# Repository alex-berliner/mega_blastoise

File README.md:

# mega_blastoise

**[▶ Play live](https://alex-berliner.github.io/mega_blastoise/battler/device.html)** — browser-based random battle simulator.
Everything published from this repo (the game, its UI notes, the hardware's 3D views) is linked from
[the site's front page](https://alex-berliner.github.io/mega_blastoise/), built from `site/`.

Layout:
- `crates/`: the Rust workspace. `ps_sim`, `ps_client`, `ps_dex`, `ps_protocol` (the Showdown
  port: server, client, dex and protocol), `ps_harness` (the protocol diff), `mega_blastoise_core` (no_std + battle data), `mega_blastoise_fw` (firmware), `mega_blastoise_test` (PC),
  and `mega_blastoise_web` (its own wasm workspace, the browser build).
- `hardware/`: the boards and cases ([index](hardware/README.md)). `docs/`: notes, including `docs/reference/architecture/`. `scripts/`: dev scripts.

Architecture overview: see [docs/reference/architecture/README.md](docs/reference/architecture/README.md).

## Documentation

Docs are in three folders: `docs/static/` (what the product is; changes only when that changes), `docs/reference/` (how it is built now) and `docs/living/` (plans, proposals and status).

- [docs/static/DESIGN.md](docs/static/DESIGN.md): what the product is, as Alex specified it. Start here
- [docs/static/next_spin_requirements.md](docs/static/next_spin_requirements.md): the next hardware spin's requirements and chosen parts
- [docs/reference/TECHNICAL.md](docs/reference/TECHNICAL.md): software internals, crate layout, interfaces, data flow
- [docs/reference/architecture/](docs/reference/architecture/README.md): deep-dive architecture docs
- [hardware/ref_design/](hardware/ref_design/README.md): the reference design (board, case, docs)
- [docs/reference/openscad-methodology.md](docs/reference/openscad-methodology.md): how the OpenSCAD cases are built and checked
- [docs/archive/v1/](docs/archive/v1/): the v1 device (Pico, two OLEDs, button matrix): its design and electronics notes.
  Its board, stripboard and case files were removed from the tree; tag `v1-archive` has them.

## Run modes (`mega-blastoise-test`)

The host binary is **interactive only**: stdin battle with the same **typed `BoardEvent` → `BoardEffects`** path as firmware (queue, prompts, combat log).

| Mode | Command | What it does |
|------|-----------|----------------|
| **Interactive** (default) | `cargo run -p mega-blastoise-test`<br>`cargo run -p mega-blastoise-test --release` | A Gen 1 battle on the PS engine over stdin (`1`-`4` a move, `s1`-`s6` a switch, when prompted). |
| **Automated tests** | `cargo test -p mega-blastoise-test` | Runs Rust tests (board-event parsing, scripted effect pipeline, host input stubs and full automated PS battles). Pass/fail exit status. |

Firmware (`mega-blastoise-fw`) has no CLI modes; flash and run as usual (see below).

## Compile

From this directory (`mega_blastoise/mega_blastoise/`, where the workspace `Cargo.toml` lives):

**PC test (host):**

```bash
cargo build -p mega-blastoise-test
cargo run -p mega-blastoise-test
```

Add `--release` to `cargo run` for a faster binary. See **Run modes** for `cargo test`.

**Firmware (Pico 2 / RP2350, the stripboard v2 board):** the Rust target is listed in
`rust-toolchain.toml`; install it by hand if rustup did not:

```bash
rustup target add thumbv8m.main-none-eabihf
```

Build from inside the firmware crate, so its `.cargo/config.toml` applies (default target
`thumbv8m.main-none-eabihf`, the linker scripts, the probe-rs runner). The default features
(`rp2350`, `board_v2`) are the device build:

```bash
cd crates/mega_blastoise_fw
cargo build
cargo build --release
cargo bv2          # same, plus the held-button overlay on the panel (input-debug)
```

**Firmware size stats** (prints section totals after link; install `rustup component add llvm-tools-preview` for `llvm-size`, or use `arm-none-eabi-size` from the GNU Arm toolchain):

```bash
./scripts/fw-build.sh                    # debug + llvm-size -t / -A
PROFILE=release ./scripts/fw-build.sh    # release build + stats
./scripts/fw-build.sh --release          # same (cargo passes --release)
```

Debug binaries include large `.debug_*` sections, so `llvm-size` totals look huge; prefer **`./scripts/fw-build.sh --release`** when checking flash/RAM against the Pico 2.

Flash/run with `probe-rs` as configured in `crates/mega_blastoise_fw/.cargo/config.toml`.

**Install `probe-rs`:** download and run the latest installer from the [probe-rs releases page](https://github.com/probe-rs/probe-rs/releases), then reload your shell:

```bash
curl --proto '=https' --tlsv1.2 -LsSf https://github.com/probe-rs/probe-rs/releases/latest/download/probe-rs-tools-installer.sh | sh
source ~/.bashrc   # or ~/.zshrc
```

Then flash with a debug probe connected (e.g. Picoprobe, CMSIS-DAP):

```bash
cd crates/mega_blastoise_fw
cargo run --release
```

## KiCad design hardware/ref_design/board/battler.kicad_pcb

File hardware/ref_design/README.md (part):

# Two-player handheld: reference design (REF-A)

A complete, orderable design for the production version of the handheld:
schematic, 2-layer board, JLCPCB fab and assembly files, a printable case, and
the documents to build, bring up and review it.

This board was first routed with `route.py 80`; 20 passes do as
well (2026-10-21: Freerouting leaves the same connections open after 15 as after 80).

**This is the 2-layer build**, on `main` since 2026-09-24: the first, 4-layer
design (kept at tag `archive/ref-design-4layer`) with every cost change Alex approved
that day, on two copper layers with JLC's standard 0.3 mm holes. Built by Claude.

## What it is

- RP2354B (2 MB flash inside), USB-C (charging + firmware + debug console)
- 3.5in 320x480 IPS panel (EastRising ER-TFT035IPS-6, ILI9488, SPI; the 2.4in ER-TFT024IPS-3 from 2026-10-21 to 2026-10-26), its FPC in a 50-pin ZIF connector (no soldering; its datasheet was not re-read when the panel came back); a
  constant-current backlight sink per LED cathode pin
- 20 membrane contacts (bare gold combs) under DS Lite silicone: a D-pad, four face buttons,
  Start and Select at each end
- PWM audio through an RC filter into an FM8002A amplifier and a 15 x 10 mm speaker that plugs in,
  lies in a hole in the board beside the screen and plays up through a grille in the face
- One 403450 Li-ion cell (about 700 mAh) in a hole in the board, its bottom in a pocket in the tub's floor, BQ24073 power-path charger,
  RT9013 3V3 LDO, soft power on seat 1's Start button with MCU hold
- Case 77.4 x 156.64 mm, 9.6 mm at the screen and 7.7 mm at the button ends
  (genuine DS Lite caps stand 1.41 mm proud there): a tub and one top piece, the whole face and sides, whose screen
  band runs from wall to wall and ends in the DS Lite's own slope; the top curves over the sides to one seam and is built upside down, printed
  face down on Bambu Support For PLA (a second filament) as its supports' interface, the tub without supports, held by six M2
  screws as a DS Lite ([case/SHELL.md](case/SHELL.md)); the board, 72.4 x 151.64 mm, is placed to
  the case's positions (`case/positions.json`); the speaker lies sunk in a hole in the board like the cell

## Folder

| Path | What |
|---|---|
| `board/design.py` | **the design as data**: every part, value, LCSC number, footprint and net. Edit this. |
| `board/placement.py` | where parts go on the board (the case supplies the rest) |
| `board/battler.kicad_pro` / `.kicad_sch` / `*.kicad_sch` / `.kicad_pcb` | the KiCad 10 project (generated) |
| `board/lib/` | project footprints and 3D models |
| `board/fab/` | gerbers zip, JLC BOM and CPL, STEP, renders, schematic and assembly PDFs: build output from `tools/fab.py`, not in git, except the renders the docs show |
| `board/tools/` | the scripts that build and check all of it (below) |
| `board/sim/` | ngspice simulation of the backlight current sinks (loop stability, accuracy, transients); `backlight_results.txt` is the last run |
| `case/case.scad` | the case, and the source of every mechanical position |
| `case/*.stl`, `case/board.dxf`, `case/positions.json` | printable parts (tub, top), board outline, positions for the board scripts: build output from `case/export.py`, not in git (run it first) |
| `case/SHELL.md` | the shell's design (the one-piece top, 2026-10-25) and why |
| `case/fitkit/` | a printable fit kit: board mock, part dummies and case coupons, to test the real parts before ordering ([its README](case/fitkit/README.md)) |
| `docs/` | [BOM](docs/bom.md) (factory and self-assembled), [assembly](docs/assembly.md), [bring-up](docs/bringup.md), [pin map](docs/pinmap.md), [design review](docs/design_review.md) |
| `tools/quotes/` | JLCPCB and PCBWay instant-quote scripts for the bare board and assembly |
| `datasheets/SOURCES.md` | where each datasheet comes from |

## Rebuilding

Everything in `board/` except `design.py`, `placement.py`, `lib/` and `tools/`
is generated. After changing the design, run the pipeline:

```sh
cd hardware/ref_design
python3 tools/build.py                       # every stage whose inputs changed since its last good run
python3 tools/build.py --list                # the stages and which are out of date
python3 tools/build.py --dry-run             # what a run would do
python3 tools/build.py --only check_fit,fitkit   # just these, always
python3 tools/build.py --from route          # route again, then whatever that changes
python3 tools/build.py --keep-going          # a failing check doesn't stop the run
python3 tools/build.py --touch               # a fresh checkout: take the committed files as built
```

It skips a stage whose command, tools and input contents match its last good run
(`.build/state.json`, not committed; logs in `.build/logs/`), so a case change that
leaves `positions.json` as it was doesn't reroute the board. The end-of-round stages
(fit kit, print packages, viewer) run only when their inputs changed; the backlight
simulation, `route.py --finish` and `sync_pcb.py` only when named with `--only`.
`tools/build.py`'s docstring has the details.

## Placement search (2026-10-27)

`board/tools/place_search.py` looks for a placement that routes clean without routing every candidate: zones first, nudges second, a quick
score instead of Freerouting, then the best candidates routed on several machines. The zones, which group may use which, the turns, the
speaker's grid and the nudge limits are data in `board/placement_zones.py`; `placement.py`'s own table is each group's home. The search's
result is `board/picks.json` (explicit poses, the core's centre and turn, the cell hole's and the speaker hole's shifts, J1's slide along
the right wall); `placement.py` applies it on top of its table, so without that file (or `PLACE_PICKS`) a build is the committed placement.

```sh
cd hardware/ref_design/board
python3 tools/place_search.py zones-png OUT.png                  # the zones and which groups may use each
python3 tools/place_search.py score ['{"poses": {...}}']       # one placement: validity and score (home by default)
python3 tools/place_search.py stage1 --out=DIR --jobs=15       # beam over the groups' zones (about 12 min on 15 cores); DIR/assign.json
python3 tools/place_search.py stage2 --out=DIR --top=40        # nudges of 0.5 to 2 mm and quarter turns; DIR/candidates.json
python3 tools/place_search.py route DIR --hosts=il:8,desktop-ubuntu:8,xps13:4 --run=NAME --prefix=P_   # route.py once per candidate, in parallel
python3 tools/place_search.py collect DIR; python3 tools/place_search.py report DIR   # re-measure the boards, list them by score
python3 tools/place_search.py stop                             # kill every run, by PID, on every host
```

Validity (a candidate is built in memory with pcbnew, no board per candidate): new courtyard overlaps (a footprint's box covers its pads),
copper 0.31 mm from the outline, the cutouts and NPTH holes, nothing in the speaker's keep-out or the cell hole, the core's escape tracks
(4.4 mm round U4's pads) inside the edge, and the case's height/zone rules (`case/check_fit.py`'s `check_part` on each moved part's cached
3D extent). `route` runs `route.py --preflight` on each candidate first and drops the ones with a placement error.
Score (lower is better): the nets that must cross each bottleneck (the gap between the hole and J3, the strips beside the hole, the board's
top end) against what fits there; the ratsnest length weighted by track width; a separate term for the power nets (VBUS, VBAT, VSYS, the LDO's
output, the backlight, the speaker); a soft penalty when U2 is more than 15 mm from J1 or J2 or the LDO more than 20 mm from the core; a
congestion count. Hosts: a host without KiCad's footprint libraries, a full JRE (Freerouting's GUI needs AWT) or xdotool gets a copy of il's
under `~/mb_route` (no install, no sudo). The case is not changed by the search itself: a candidate that moves the speaker, J1 along its wall,
the cell hole or BOOT/RESET needs a case respin (`case/case.scad`) before it is adopted.

Speed: `tools/scad.py` picks OpenSCAD. With an OpenSCAD development snapshot AppImage
in `~/Applications` (openscad.org, Development Snapshots) it renders with the Manifold
backend, minutes down to seconds; otherwise the system `openscad` (CGAL). `OPENSCAD=...`
picks a binary, `OPENSCAD_BACKEND=CGAL` the old backend. Renders and kicad-cli exports
run several at once (`REF_JOBS` sets how many). `route.py` first runs a pre-flight (the placed board with the pre-routes on it through the DRC, about 4 s; it aborts with the
list when an error is not the router's: `--no-preflight` skips it, `--preflight` only runs it), then routes copies of the
board at once, each handed to Freerouting in another order (`--seed=`: 1.9 routes one file the same way every time, so
identical copies all end the same way): half the cores, at most 8 (`--attempts=N` or `ROUTE_ATTEMPTS`, 1 routes in place; a
run holds about 1.5 cores and 1 GB). The first copy with a clean DRC is kept and the others killed; one with 2 or fewer open
and 3 or fewer errors gets `--finish` on a copy while the rest keep going; anything still running at twice the first
finisher's time is killed. `--exhaustive` is the old policy (4 at once, the next seed when one ends with something open,
`--tries=M` caps the seeds, default 2N).
Freerouting gets 20 passes (it gains nothing after about 15), no 20 s start-up dialog and
no optimizer pass (`--optimize` puts it back); about 4.5 min for a clean board where three
80-pass attempts took over 10.

Waiting on long jobs (routing, slicing): wait on the job's PID or on a done-marker file, not
on its name. `pgrep -f "print_package.py 1_case"` inside `bash -c "..."` matches the waiting
shell's own command line, so the loop only ends at its cap (8.5 min lost on 2026-10-26).

```sh
python3 case/print_package.py --slice > /tmp/pk.log 2>&1 & echo $! > /tmp/pk.pid
tools/wait_done.sh --pid "$(cat /tmp/pk.pid)" --timeout 1800     # 0 done, 124 timed out
(python3 tools/build.py; touch /tmp/build.done) &                 # or end the job with a marker
tools/wait_done.sh --file /tmp/build.done --timeout 1800
```

If `pgrep -f` is unavoidable, bracket the first letter so the pattern doesn't match itself:
`pgrep -f "[p]rint_package.py"`.

Print kits: `python3 tools/build.py` only writes them (the release zips hold the case plates, `1_case` and `5_unit`;
the P1S splits `5_unit` into a and b), in seconds. `python3 tools/build.py --slice` (or `RELEASE=1`) slices them too, U1
and P1S at the same time (`SLICE_JOBS` slicers each, default cores/8), and keeps each sliced plate in `case/print/.slice_cache/`
(not in git; key: its STLs, the profiles, the packagers' sources and the slicer), so a second run with nothing changed
takes seconds. By hand: `python3 case/print_package.py [--slice] [--no-cache] [plate ...]` and `case/print_package_p1s.py`
likewise; no plate named is the release kit, named plates (or `--all`) build instead, the printer tests go to
`overhang_kit.zip` and the other plates (fit coupons, button tunings) to `case/print/extras_U1/` and `extras_P1S/`.
Every case build has a version (`case/VERSION`, `C<n>`), debossed inside the tub and the top and in the release zip's name
(`mega_blastoise_print_U1_C1.zip`); the release kit is refused unless `case/` is committed, so a version is one commit. How to
cut the next one: `case/SHELL.md`, "The version".

The stages, by hand:

```sh
cd hardware/ref_design
python3 case/export.py --stl                 # case -> positions.json, DXF, tub/top STLs
python3 case/check_buttons.py                # D-pad, A/B/X/Y, Start/Select with their silicone under the shell
cd board
python3 tools/build_sch.py                   # design.py -> schematic (tools/schwrite.py writes the sheets)
python3 tools/check_netlist.py               # KiCad's netlist == design.py ?
python3 tools/check_pins.py                  # every part's pins against its datasheet review (pin_review/)
python3 sim/models.py && python3 sim/backlight.py   # backlight sink stability (ngspice, about 40 min; only when it changes)
kicad-cli sch erc battler.kicad_sch          # 0 errors expected
RP2350B_REF=.../RPI-RP2350B-MINIMAL_R4-S1.kicad_pcb python3 tools/build_pcb.py
FREEROUTING_JAR=.../freerouting-1.9.0.jar python3 tools/route.py   # about 7 min on 16 cores, 8 seeded attempts at once, stops at the first clean one
python3 tools/route.py --finish              # only if route.py left a connection open
python3 tools/silk.py
python3 tools/sync_pcb.py                    # only for a redrawn schematic on a routed board: relink, rename nets
python3 tools/check_pcb.py                   # DRC with schematic parity
python3 tools/fab.py                         # gerbers, BOM, CPL, STEP, renders
python3 ../case/check_fit.py                 # board inside the case?
python3 ../case/fitkit.py                    # the printable fit kit (under a minute with Manifold)
python3 ../case/check_manifold.py            # every printed part's mesh manifold (each edge on two faces)?
python3 ../case/check_wall.py                # the top's wall under its side rounds thick enough (about 2 min)?
python3 tools/pinmap.py                      # docs/pinmap.md
python3 tools/strip_load.py                  # nets through each strip beside the cell's hole, ratsnest length (no routing)
python3 ../viewer/build.py                   # the exploded 3D view (GitHub Pages, /assembly/)
```

The exploded view is published at https://alex-berliner.github.io/mega_blastoise/assembly/
whenever main is pushed. Its parts are built here (GitHub's runners lack KiCad's 3D
library and OpenSCAD) and committed; `viewer/pre-push`, installed as the repo's pre-push
hook, rebuilds and commits them when main would go out with stale ones.

Needs KiCad 10 (kicad-cli and its `pcbnew` Python module), OpenSCAD, Java,
Freerouting 1.9.0, and Raspberry Pi's RP2350B minimal KiCad design
(document RP-010329-CA) for the core layout. The project library in `lib/` is
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
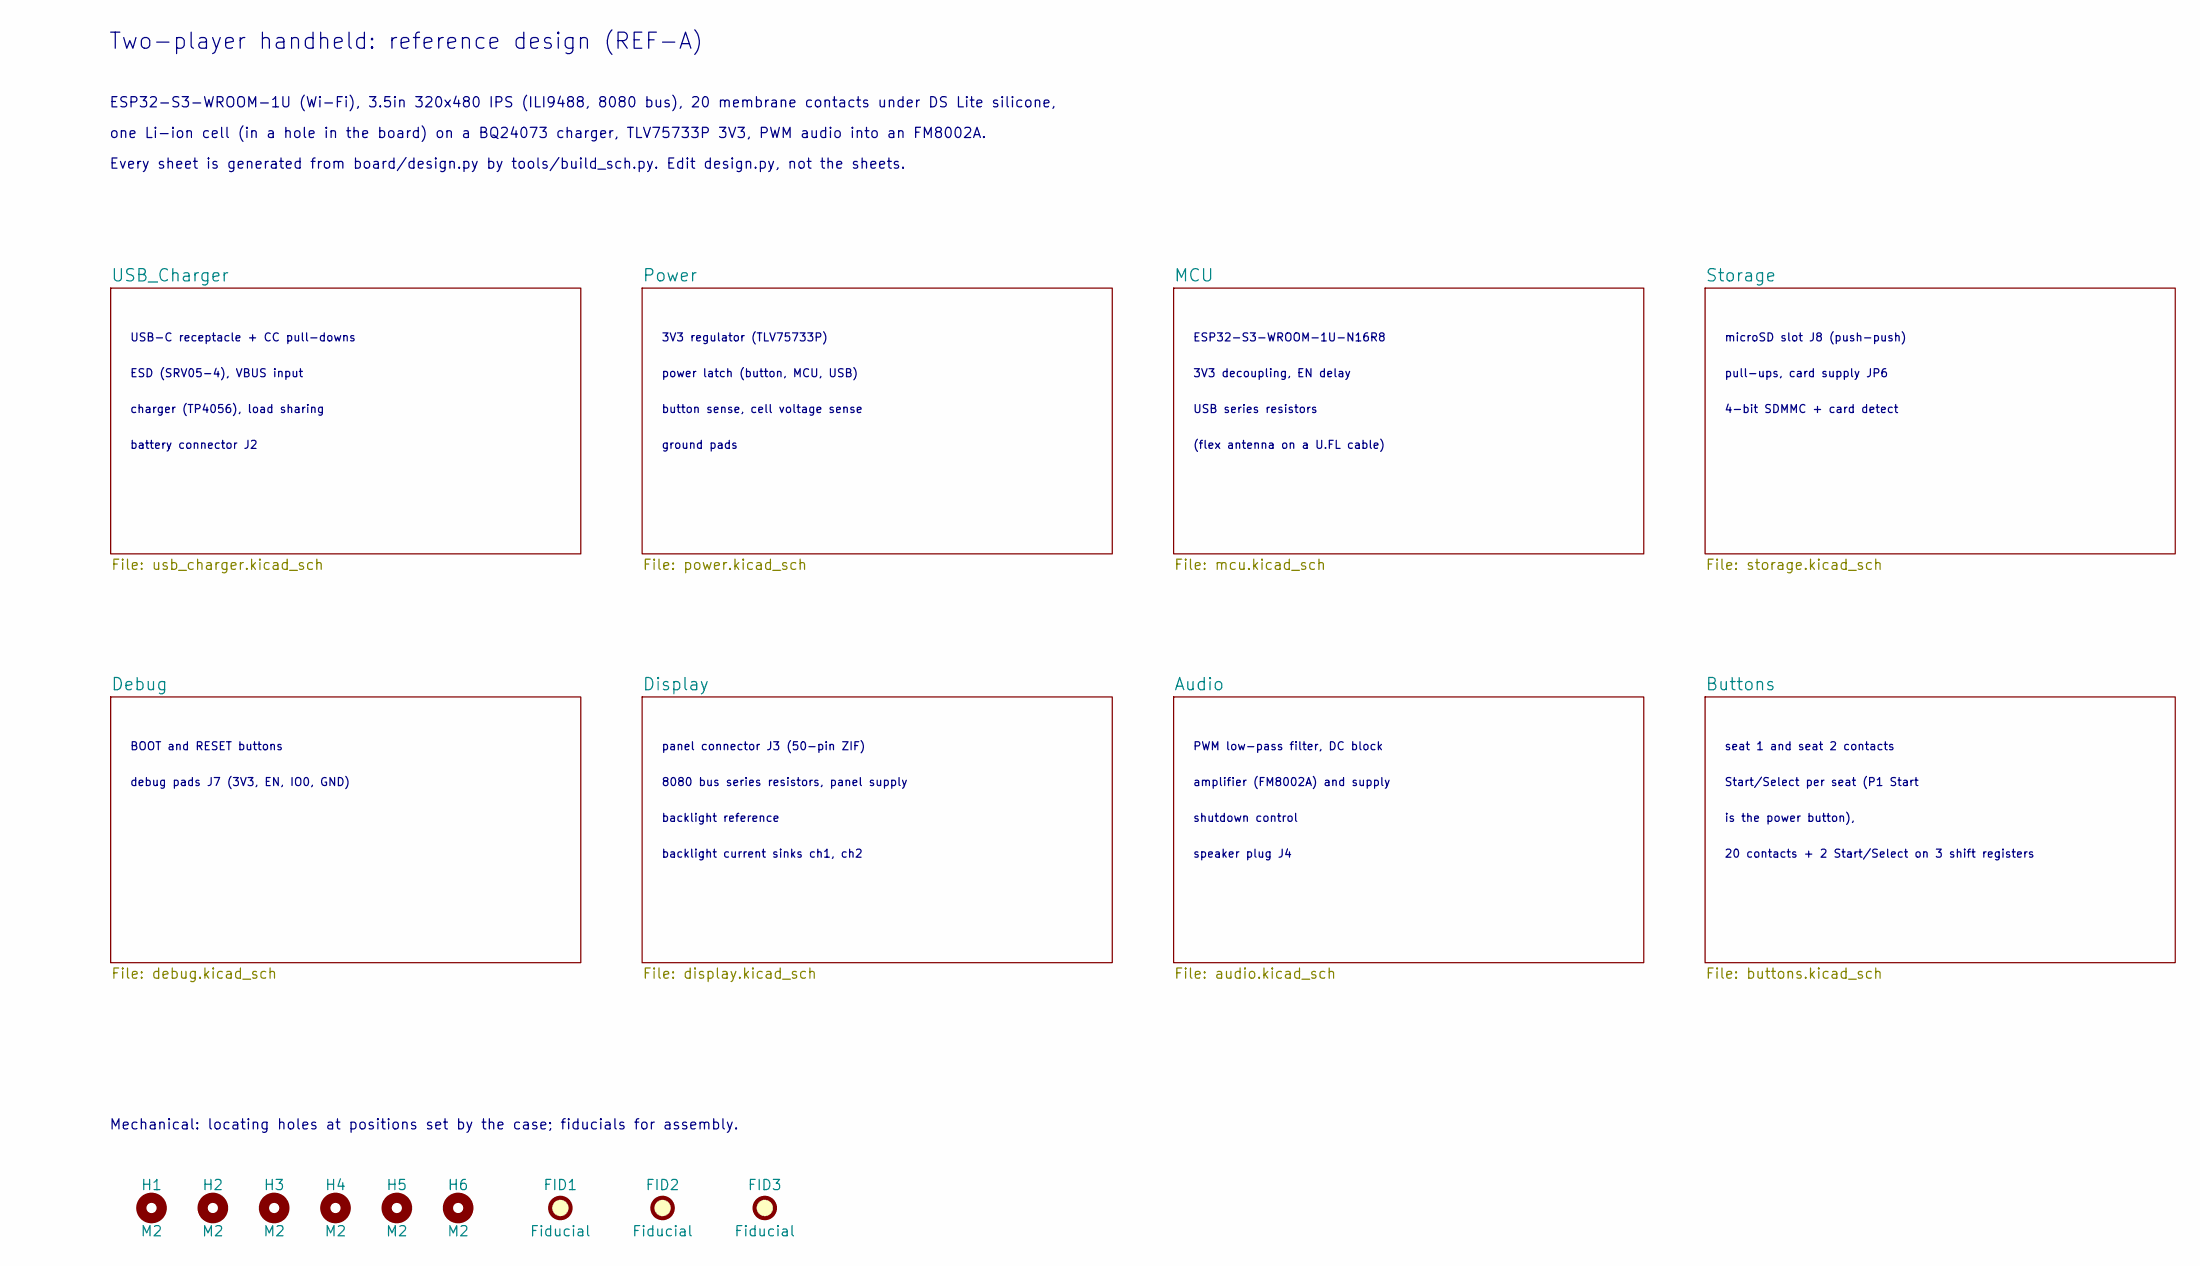
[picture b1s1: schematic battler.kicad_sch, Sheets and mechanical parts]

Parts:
FID1, FID2, FID3: Fiducial; Fiducial_1mm_Mask2mm
H1, H2, H3, H4, H5, H6: M2; MountingHole_2.2mm_M2

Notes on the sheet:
Two-player handheld: reference design (REF-A)
ESP32-S3-WROOM-1U (Wi-Fi), 3.5in 320x480 IPS (ILI9488, 8080 bus), 20 membrane contacts under DS Lite silicone,
one Li-ion cell (in a hole in the board) on a BQ24073 charger, TLV75733P 3V3, PWM audio into an FM8002A.
Every sheet is generated from board/design.py by tools/build_sch.py. Edit design.py, not the sheets.
USB-C receptacle + CC pull-downs
ESD (SRV05-4), VBUS input
charger (TP4056), load sharing
battery connector J2
3V3 regulator (TLV75733P)
power latch (button, MCU, USB)
button sense, cell voltage sense
ground pads
ESP32-S3-WROOM-1U-N16R8
3V3 decoupling, EN delay
USB series resistors
(flex antenna on a U.FL cable)
microSD slot J8 (push-push)
pull-ups, card supply JP6
4-bit SDMMC + card detect
BOOT and RESET buttons
debug pads J7 (3V3, EN, IO0, GND)
panel connector J3 (50-pin ZIF)
8080 bus series resistors, panel supply
backlight reference
backlight current sinks ch1, ch2
PWM low-pass filter, DC block
amplifier (FM8002A) and supply
shutdown control
speaker plug J4
seat 1 and seat 2 contacts
Start/Select per seat (P1 Start
is the power button),
20 contacts + 2 Start/Select on 3 shift registers
Mechanical: locating holes at positions set by the case; fiducials for assembly.

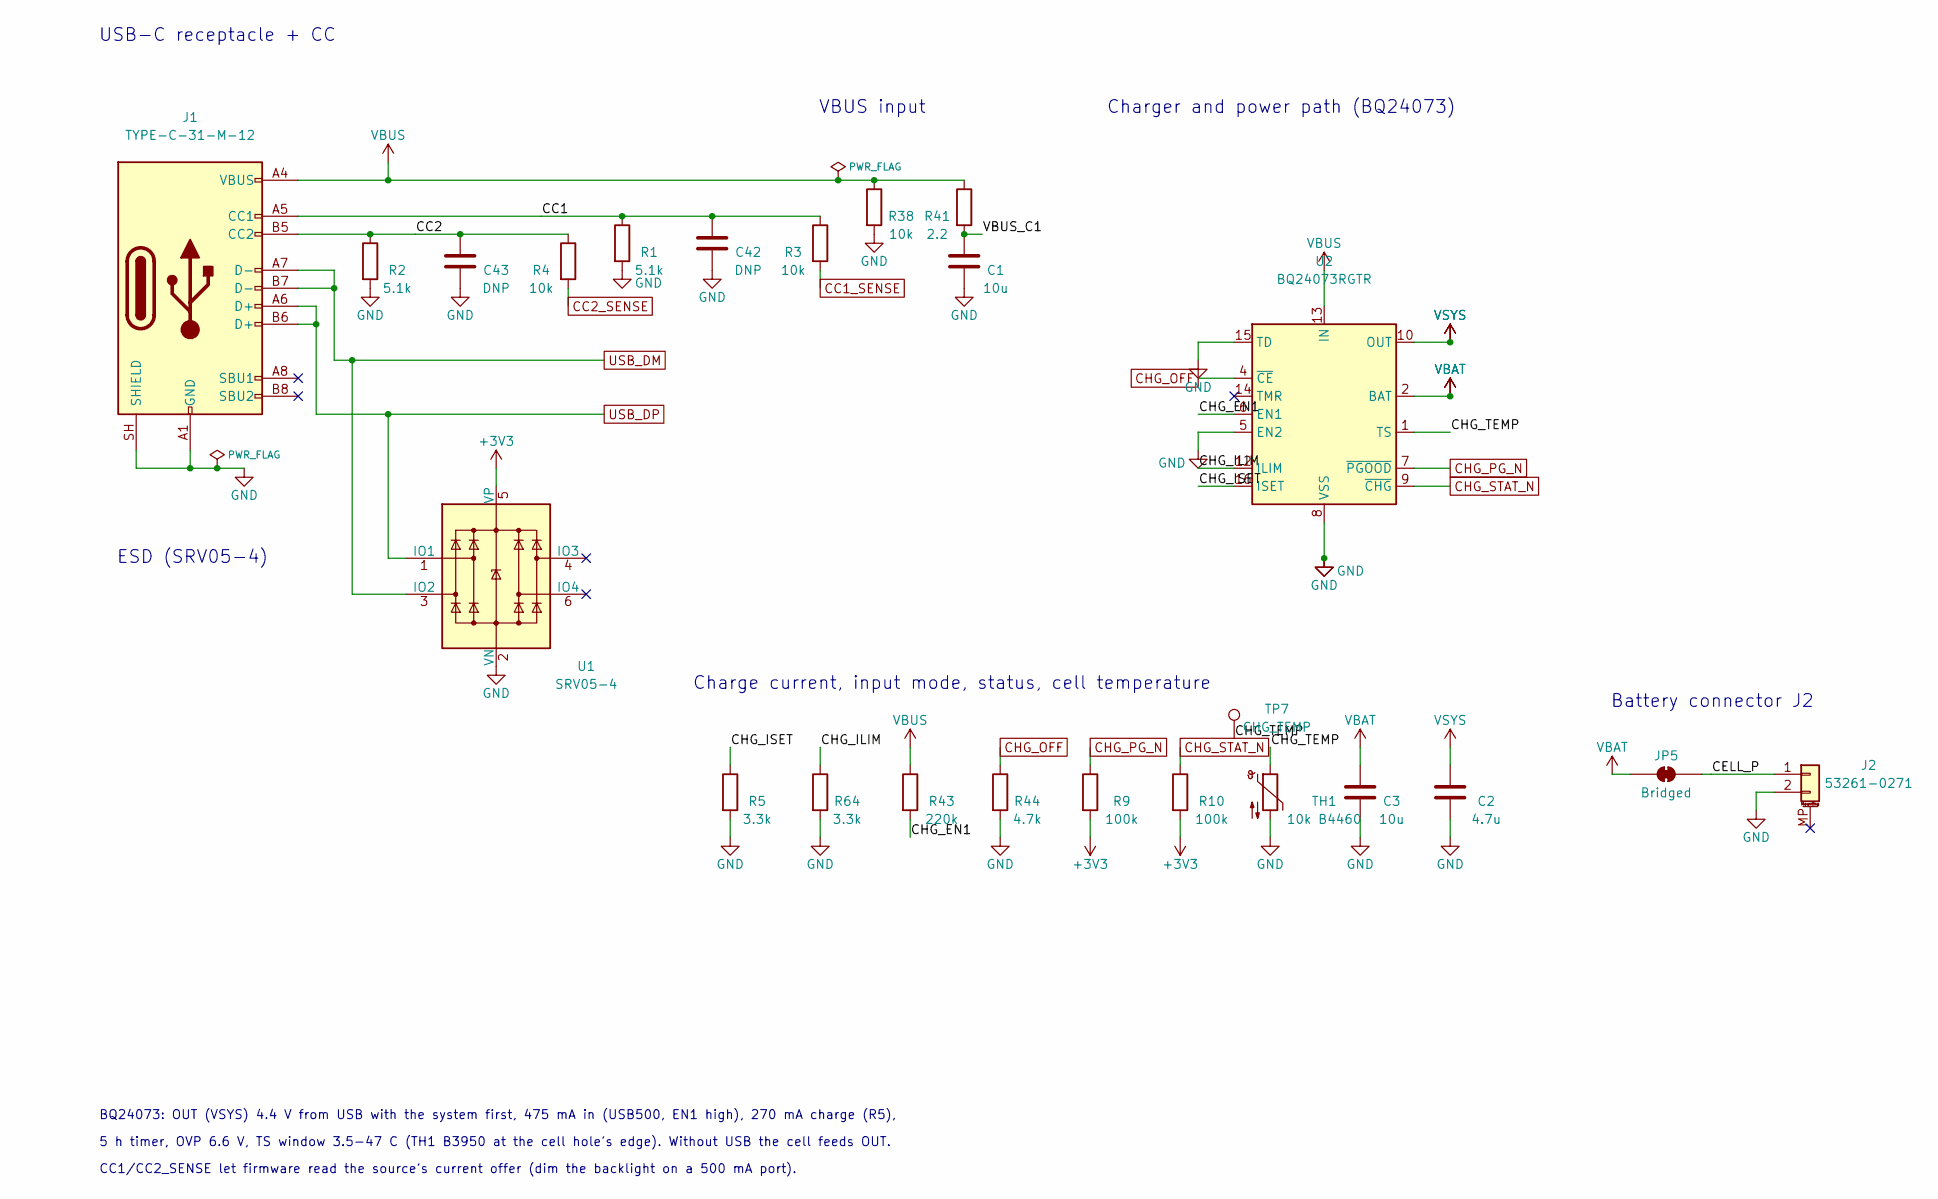
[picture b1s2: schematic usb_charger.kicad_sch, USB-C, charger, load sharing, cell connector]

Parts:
C1: 10u; C_0603_1608Metric; MPN CL10A106MA8NRNC; LCSC C96446
C2: 4.7u; C_0603_1608Metric; MPN CL10A475KO8NNNC; LCSC C19666
C3: 10u; C_0603_1608Metric; MPN CL10A106KP8NNNC; LCSC C19702
C42, C43: DNP; C_1206_3216Metric
J1: TYPE-C-31-M-12; USB_C_Receptacle_HRO_TYPE-C-31-M-12; MPN TYPE-C-31-M-12; LCSC C165948
J2: 53261-0271; Molex_PicoBlade_53261-0271_1x02-1MP_P1.25mm_Horizontal; MPN 532610271; LCSC C177225
JP5: Bridged; SolderJumper-2_P1.3mm_Bridged_Pad1.0x1.5mm
R1, R2: 5.1k; R_0402_1005Metric; MPN 0402WGF5101TCE; LCSC C25905
R3, R4, R38: 10k; R_0402_1005Metric; MPN 0402WGF1002TCE; LCSC C25744
R5, R64: 3.3k; R_0402_1005Metric; MPN 0402WGF3301TCE; LCSC C25890
R9, R10: 100k; R_0402_1005Metric; MPN 0402WGF1003TCE; LCSC C25741
R41: 2.2; R_0603_1608Metric; MPN 0603WAF220KT5E; LCSC C22939
R43: 220k; R_0402_1005Metric; MPN 0402WGF2203TCE; LCSC C25767
R44: 4.7k; R_0402_1005Metric; MPN 0402WGF4701TCE; LCSC C25900
TH1: 10k B4460; R_0805_2012Metric; MPN TCTR0805F10K0F4460T; LCSC C525375
TP7: CHG_TEMP; TestPoint_Pad_D1.0mm
U1: SRV05-4; SOT-23-6; MPN SRV05-4.TCT; LCSC C13612
U2: BQ24073RGTR; VQFN-16-1EP_3x3mm_RGT0016C; MPN BQ24073RGTR; LCSC C15220

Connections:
+3V3: R9.2, R10.2, U1.5 (VP); also elsewhere on the board
/USB_Charger/CC1: C42.1, J1.A5 (CC1), R1.1, R3.1
/USB_Charger/CC2: C43.1, J1.B5 (CC2), R2.1, R4.1
/USB_Charger/CELL_P: J2.1, JP5.1 (A)
/USB_Charger/CHG_EN1: R43.2, U2.6 (EN1)
/USB_Charger/CHG_ILIM: R64.1, U2.12 (ILIM)
/USB_Charger/CHG_ISET: R5.1, U2.16 (ISET)
/USB_Charger/CHG_TEMP: TH1.1, TP7.1, U2.1 (TS)
/USB_Charger/VBUS_C1: C1.1, R41.2
CC1_SENSE: R3.2; also elsewhere on the board
CC2_SENSE: R4.2; also elsewhere on the board
CHG_OFF: R44.1, U2.4 (~CE); also elsewhere on the board
CHG_PG_N: R9.1, U2.7 (~PGOOD); also elsewhere on the board
CHG_STAT_N: R10.1, U2.9 (~CHG); also elsewhere on the board
GND: C1.2, C2.2, C3.2, C42.2, C43.2, J1.A1 (GND), J1.A12 (GND), J1.B1 (GND), J1.B12 (GND), J1.SH (SHIELD), J2.2, R1.2, R2.2, R5.2, R38.2, R44.2, R64.2, TH1.2, U1.2 (VN), U2.5 (EN2), U2.8 (VSS), U2.15 (TD), U2.17 (VSS); also elsewhere on the board
USB_DM: J1.A7 (D-), J1.B7 (D-), U1.3 (IO2); also elsewhere on the board
USB_DP: J1.A6 (D+), J1.B6 (D+), U1.1 (IO1); also elsewhere on the board
VBAT: C3.1, JP5.2 (B), U2.2 (BAT), U2.3 (BAT); also elsewhere on the board
VBUS: J1.A4 (VBUS), J1.A9 (VBUS), J1.B4 (VBUS), J1.B9 (VBUS), R38.1, R41.1, R43.1, U2.13 (IN); also elsewhere on the board
VSYS: C2.1, U2.10 (OUT), U2.11 (OUT); also elsewhere on the board

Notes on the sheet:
USB-C receptacle + CC
ESD (SRV05-4)
VBUS input
Charger and power path (BQ24073)
Charge current, input mode, status, cell temperature
Battery connector J2
BQ24073: OUT (VSYS) 4.4 V from USB with the system first, 475 mA in (USB500, EN1 high), 270 mA charge (R5),
5 h timer, OVP 6.6 V, TS window 3.5-47 C (TH1 B3950 at the cell hole's edge). Without USB the cell feeds OUT.
CC1/CC2_SENSE let firmware read the source's current offer (dim the backlight on a 500 mA port).

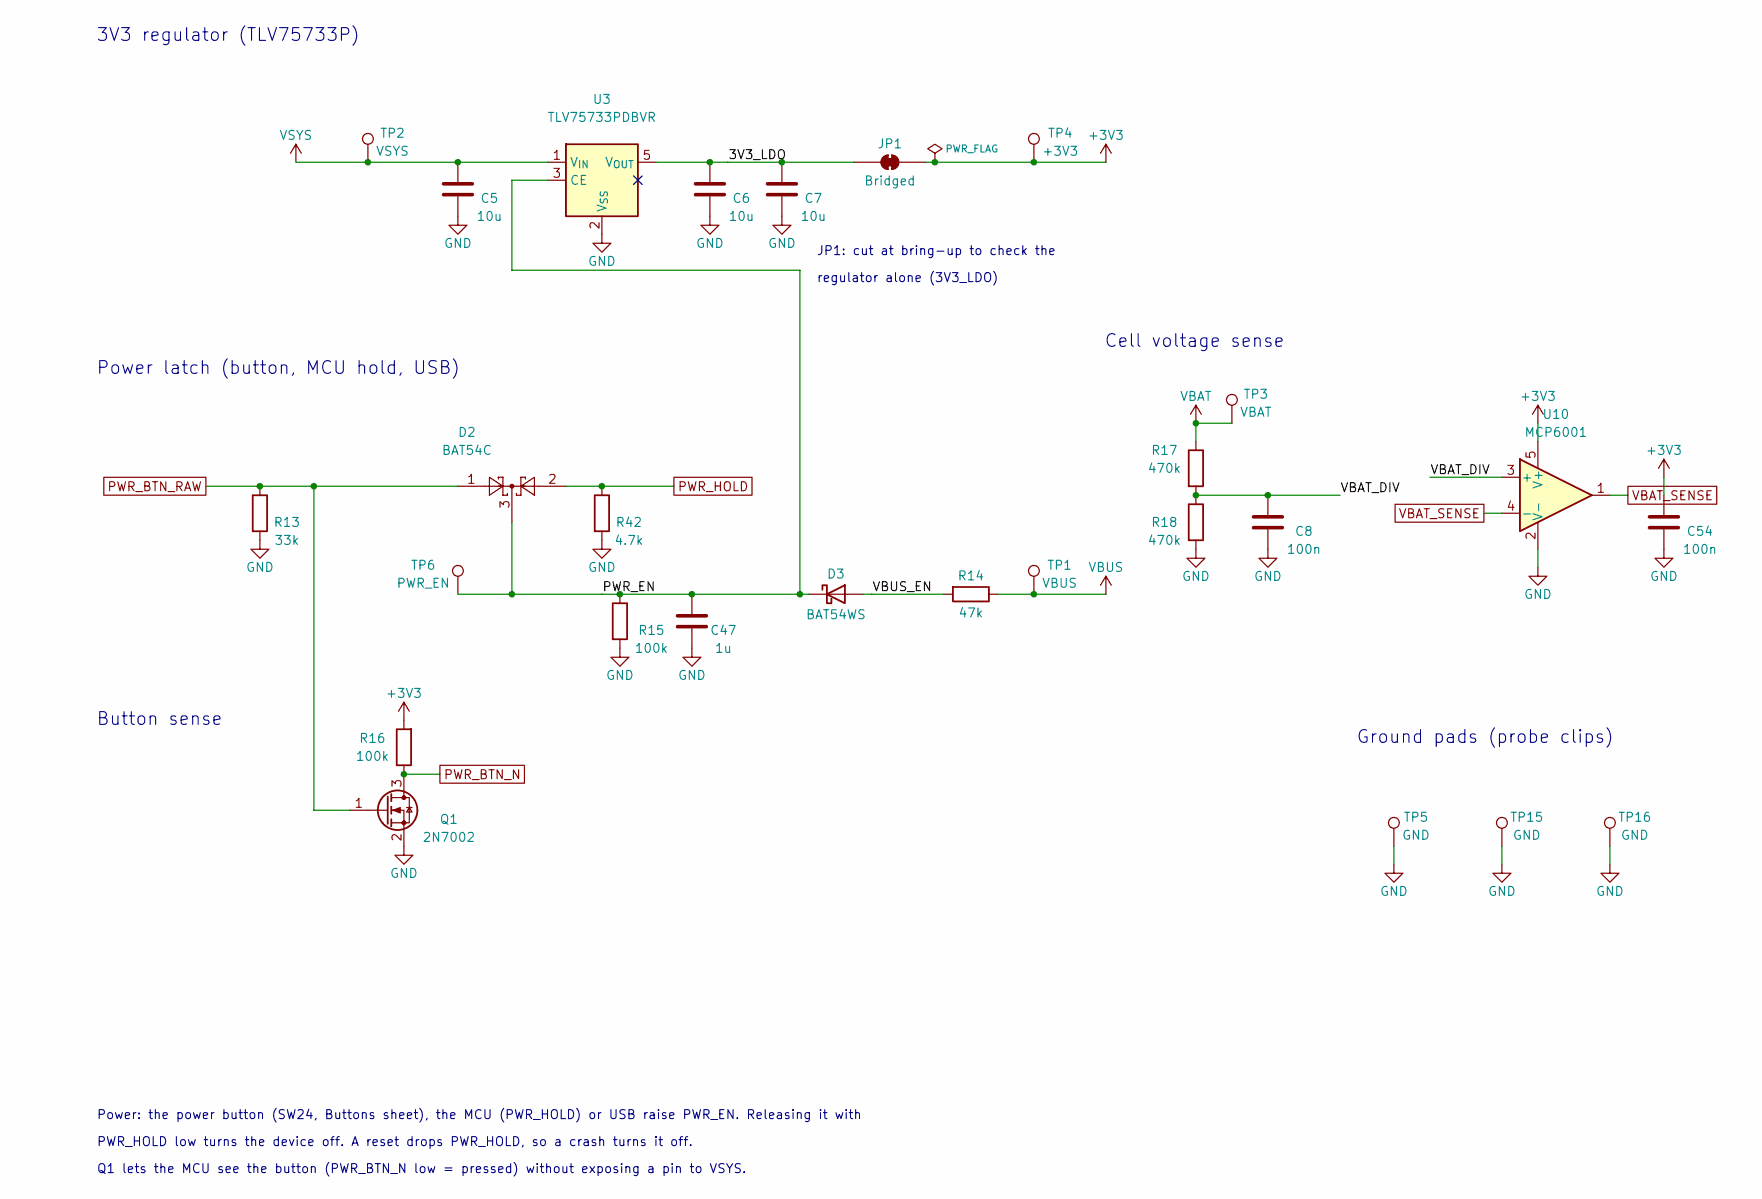
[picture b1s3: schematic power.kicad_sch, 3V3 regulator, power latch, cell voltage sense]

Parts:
C5, C6, C7: 10u; C_0603_1608Metric; MPN CL10A106KP8NNNC; LCSC C19702
C8, C54: 100n; C_0402_1005Metric; MPN CL05B104KO5NNNC; LCSC C1525
C47: 1u; C_0402_1005Metric; MPN CL05A105KA5NQNC; LCSC C52923
D2: BAT54C; SOT-23; MPN BAT54C,215; LCSC C37704
D3: BAT54WS; D_SOD-323; MPN BAT54WS; LCSC C7502694
JP1: Bridged; SolderJumper-2_P1.3mm_Bridged_Pad1.0x1.5mm
Q1: 2N7002; SOT-23; MPN 2N7002; LCSC C8545
R13: 33k; R_0402_1005Metric; MPN 0402WGF3302TCE; LCSC C25779
R14: 47k; R_0402_1005Metric; MPN 0402WGF4702TCE; LCSC C25792
R15, R16: 100k; R_0402_1005Metric; MPN 0402WGF1003TCE; LCSC C25741
R17, R18: 470k; R_0402_1005Metric; MPN 0402WGF4703TCE; LCSC C25790
R42: 4.7k; R_0402_1005Metric; MPN 0402WGF4701TCE; LCSC C25900
TP1: VBUS; TestPoint_Pad_D1.0mm
TP2: VSYS; TestPoint_Pad_D1.0mm
TP3: VBAT; TestPoint_Pad_D1.0mm
TP4: +3V3; TestPoint_Pad_D1.0mm
TP5, TP15, TP16: GND; TestPoint_Pad_D1.0mm
TP6: PWR_EN; TestPoint_Pad_D1.0mm
U3: TLV75733PDBVR; SOT-23-5; MPN TLV75733PDBVR; LCSC C485517
U10: MCP6001; SOT-23-5; MPN MCP6001T-I/OT; LCSC C116490

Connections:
+3V3: C54.1, JP1.2 (B), R16.2, TP4.1, U10.5 (V+); also elsewhere on the board
/Power/3V3_LDO: C6.1, C7.1, JP1.1 (A), U3.5 (V_{OUT})
/Power/PWR_EN: C47.1, D2.3, D3.1 (K), R15.1, TP6.1, U3.3 (CE)
/Power/VBAT_DIV: C8.1, R17.2, R18.1, U10.3 (+)
/Power/VBUS_EN: D3.2 (A), R14.2
GND: C5.2, C6.2, C7.2, C8.2, C47.2, C54.2, Q1.2 (S), R13.2, R15.2, R18.2, R42.2, TP5.1, TP15.1, TP16.1, U3.2 (V_{SS}), U10.2 (V-); also elsewhere on the board
PWR_BTN_N: Q1.3 (D), R16.1; also elsewhere on the board
PWR_BTN_RAW: D2.1, Q1.1 (G), R13.1; also elsewhere on the board
PWR_HOLD: D2.2, R42.1; also elsewhere on the board
VBAT: R17.1, TP3.1; also elsewhere on the board
VBAT_SENSE: U10.1, U10.4 (-); also elsewhere on the board
VBUS: R14.1, TP1.1; also elsewhere on the board
VSYS: C5.1, TP2.1, U3.1 (V_{IN}); also elsewhere on the board

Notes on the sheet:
3V3 regulator (TLV75733P)
JP1: cut at bring-up to check the
regulator alone (3V3_LDO)
Power latch (button, MCU hold, USB)
Button sense
Cell voltage sense
Ground pads (probe clips)
Power: the power button (SW24, Buttons sheet), the MCU (PWR_HOLD) or USB raise PWR_EN. Releasing it with
PWR_HOLD low turns the device off. A reset drops PWR_HOLD, so a crash turns it off.
Q1 lets the MCU see the button (PWR_BTN_N low = pressed) without exposing a pin to VSYS.

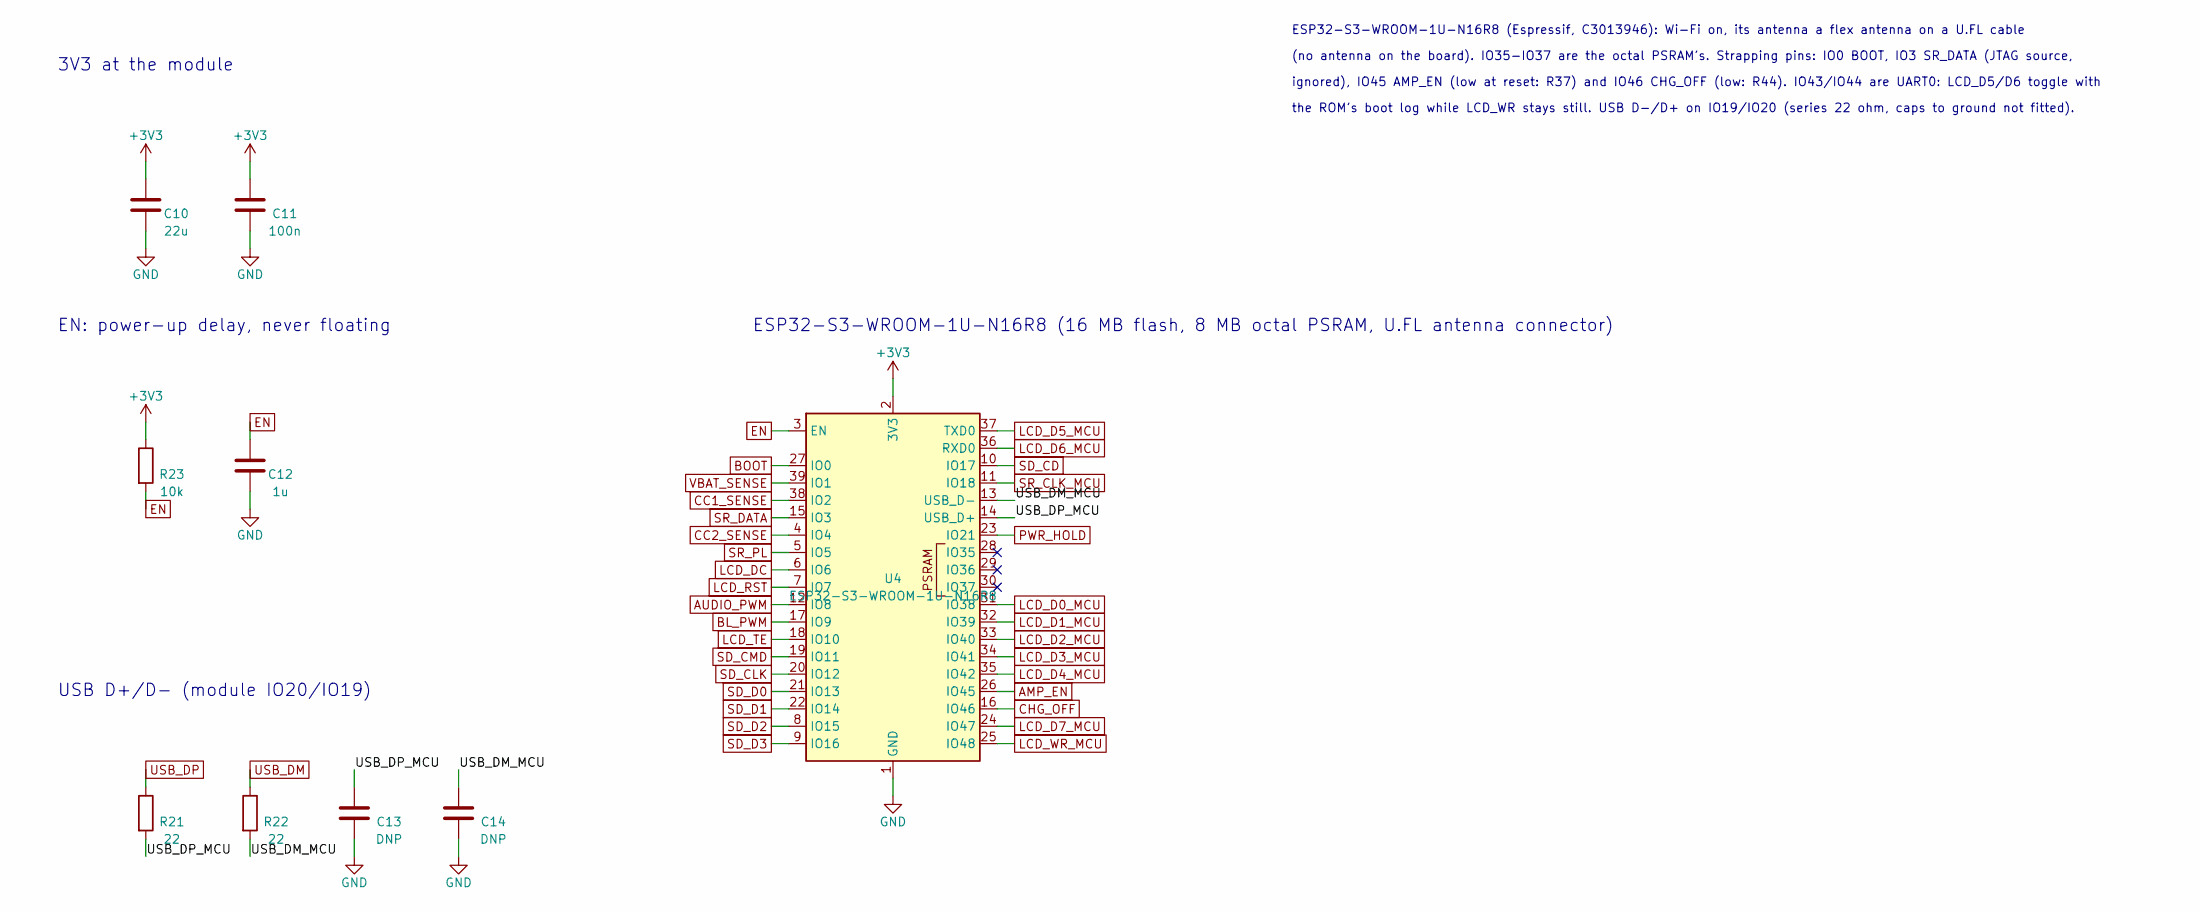
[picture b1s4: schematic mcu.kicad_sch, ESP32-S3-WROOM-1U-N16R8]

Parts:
C10: 22u; C_0805_2012Metric; MPN CL21A226MAQNNNE; LCSC C45783
C11: 100n; C_0402_1005Metric; MPN CL05B104KO5NNNC; LCSC C1525
C12: 1u; C_0402_1005Metric; MPN CL05A105KA5NQNC; LCSC C52923
C13, C14: DNP; C_0402_1005Metric
R21, R22: 22; R_0402_1005Metric; MPN 0402WGF220JTCE; LCSC C25092
R23: 10k; R_0402_1005Metric; MPN 0402WGF1002TCE; LCSC C25744
U4: ESP32-S3-WROOM-1U-N16R8; ESP32-S3-WROOM-1U; MPN ESP32-S3-WROOM-1U-N16R8; LCSC C3013946

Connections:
+3V3: C10.1, C11.1, R23.1, U4.2 (3V3); also elsewhere on the board
/MCU/USB_DM_MCU: C14.1, R22.2, U4.13 (USB_D-)
/MCU/USB_DP_MCU: C13.1, R21.2, U4.14 (USB_D+)
AMP_EN: U4.26 (IO45); also elsewhere on the board
AUDIO_PWM: U4.12 (IO8); also elsewhere on the board
BL_PWM: U4.17 (IO9); also elsewhere on the board
BOOT: U4.27 (IO0); also elsewhere on the board
CC1_SENSE: U4.38 (IO2); also elsewhere on the board
CC2_SENSE: U4.4 (IO4); also elsewhere on the board
CHG_OFF: U4.16 (IO46); also elsewhere on the board
EN: C12.1, R23.2, U4.3 (EN); also elsewhere on the board
GND: C10.2, C11.2, C12.2, C13.2, C14.2, U4.1 (GND), U4.40 (GND), U4.41 (GND); also elsewhere on the board
LCD_D0_MCU: U4.31 (IO38); also elsewhere on the board
LCD_D1_MCU: U4.32 (IO39); also elsewhere on the board
LCD_D2_MCU: U4.33 (IO40); also elsewhere on the board
LCD_D3_MCU: U4.34 (IO41); also elsewhere on the board
LCD_D4_MCU: U4.35 (IO42); also elsewhere on the board
LCD_D5_MCU: U4.37 (TXD0); also elsewhere on the board
LCD_D6_MCU: U4.36 (RXD0); also elsewhere on the board
LCD_D7_MCU: U4.24 (IO47); also elsewhere on the board
LCD_DC: U4.6 (IO6); also elsewhere on the board
LCD_RST: U4.7 (IO7); also elsewhere on the board
LCD_TE: U4.18 (IO10); also elsewhere on the board
LCD_WR_MCU: U4.25 (IO48); also elsewhere on the board
PWR_HOLD: U4.23 (IO21); also elsewhere on the board
SD_CD: U4.10 (IO17); also elsewhere on the board
SD_CLK: U4.20 (IO12); also elsewhere on the board
SD_CMD: U4.19 (IO11); also elsewhere on the board
SD_D0: U4.21 (IO13); also elsewhere on the board
SD_D1: U4.22 (IO14); also elsewhere on the board
SD_D2: U4.8 (IO15); also elsewhere on the board
SD_D3: U4.9 (IO16); also elsewhere on the board
SR_CLK_MCU: U4.11 (IO18); also elsewhere on the board
SR_DATA: U4.15 (IO3); also elsewhere on the board
SR_PL: U4.5 (IO5); also elsewhere on the board
USB_DM: R22.1; also elsewhere on the board
USB_DP: R21.1; also elsewhere on the board
VBAT_SENSE: U4.39 (IO1); also elsewhere on the board

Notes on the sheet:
ESP32-S3-WROOM-1U-N16R8 (16 MB flash, 8 MB octal PSRAM, U.FL antenna connector)
3V3 at the module
EN: power-up delay, never floating
USB D+/D- (module IO20/IO19)
ESP32-S3-WROOM-1U-N16R8 (Espressif, C3013946): Wi-Fi on, its antenna a flex antenna on a U.FL cable
(no antenna on the board). IO35-IO37 are the octal PSRAM's. Strapping pins: IO0 BOOT, IO3 SR_DATA (JTAG source,
ignored), IO45 AMP_EN (low at reset: R37) and IO46 CHG_OFF (low: R44). IO43/IO44 are UART0: LCD_D5/D6 toggle with
the ROM's boot log while LCD_WR stays still. USB D-/D+ on IO19/IO20 (series 22 ohm, caps to ground not fitted).

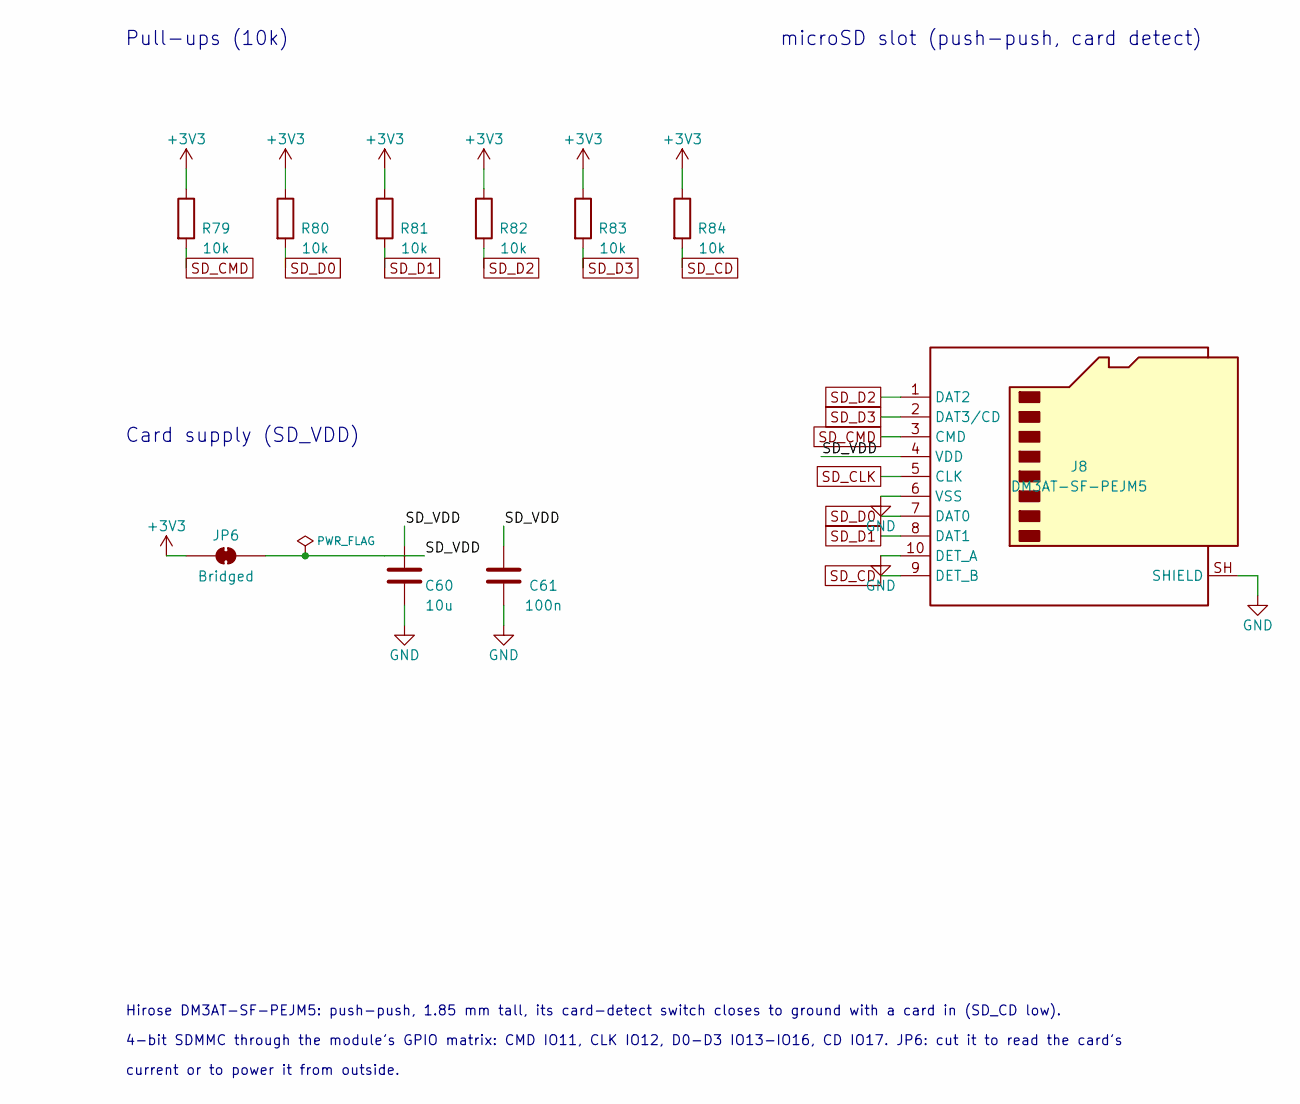
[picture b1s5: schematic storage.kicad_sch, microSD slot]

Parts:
C60: 10u; C_0603_1608Metric; MPN CL10A106KP8NNNC; LCSC C19702
C61: 100n; C_0402_1005Metric; MPN CL05B104KO5NNNC; LCSC C1525
J8: DM3AT-SF-PEJM5; microSD_HC_Hirose_DM3AT-SF-PEJM5; MPN DM3AT-SF-PEJM5; LCSC C114218
JP6: Bridged; SolderJumper-2_P1.3mm_Bridged_Pad1.0x1.5mm
R79, R80, R81, R82, R83, R84: 10k; R_0402_1005Metric; MPN 0402WGF1002TCE; LCSC C25744

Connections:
+3V3: JP6.1 (A), R79.1, R80.1, R81.1, R82.1, R83.1, R84.1; also elsewhere on the board
/Storage/SD_VDD: C60.1, C61.1, J8.4 (VDD), JP6.2 (B)
GND: C60.2, C61.2, J8.6 (VSS), J8.10 (DET_A), J8.SH (SHIELD); also elsewhere on the board
SD_CD: J8.9 (DET_B), R84.2; also elsewhere on the board
SD_CLK: J8.5 (CLK); also elsewhere on the board
SD_CMD: J8.3 (CMD), R79.2; also elsewhere on the board
SD_D0: J8.7 (DAT0), R80.2; also elsewhere on the board
SD_D1: J8.8 (DAT1), R81.2; also elsewhere on the board
SD_D2: J8.1 (DAT2), R82.2; also elsewhere on the board
SD_D3: J8.2 (DAT3/CD), R83.2; also elsewhere on the board

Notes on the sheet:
microSD slot (push-push, card detect)
Pull-ups (10k)
Card supply (SD_VDD)
Hirose DM3AT-SF-PEJM5: push-push, 1.85 mm tall, its card-detect switch closes to ground with a card in (SD_CD low).
4-bit SDMMC through the module's GPIO matrix: CMD IO11, CLK IO12, D0-D3 IO13-IO16, CD IO17. JP6: cut it to read the card's
current or to power it from outside.

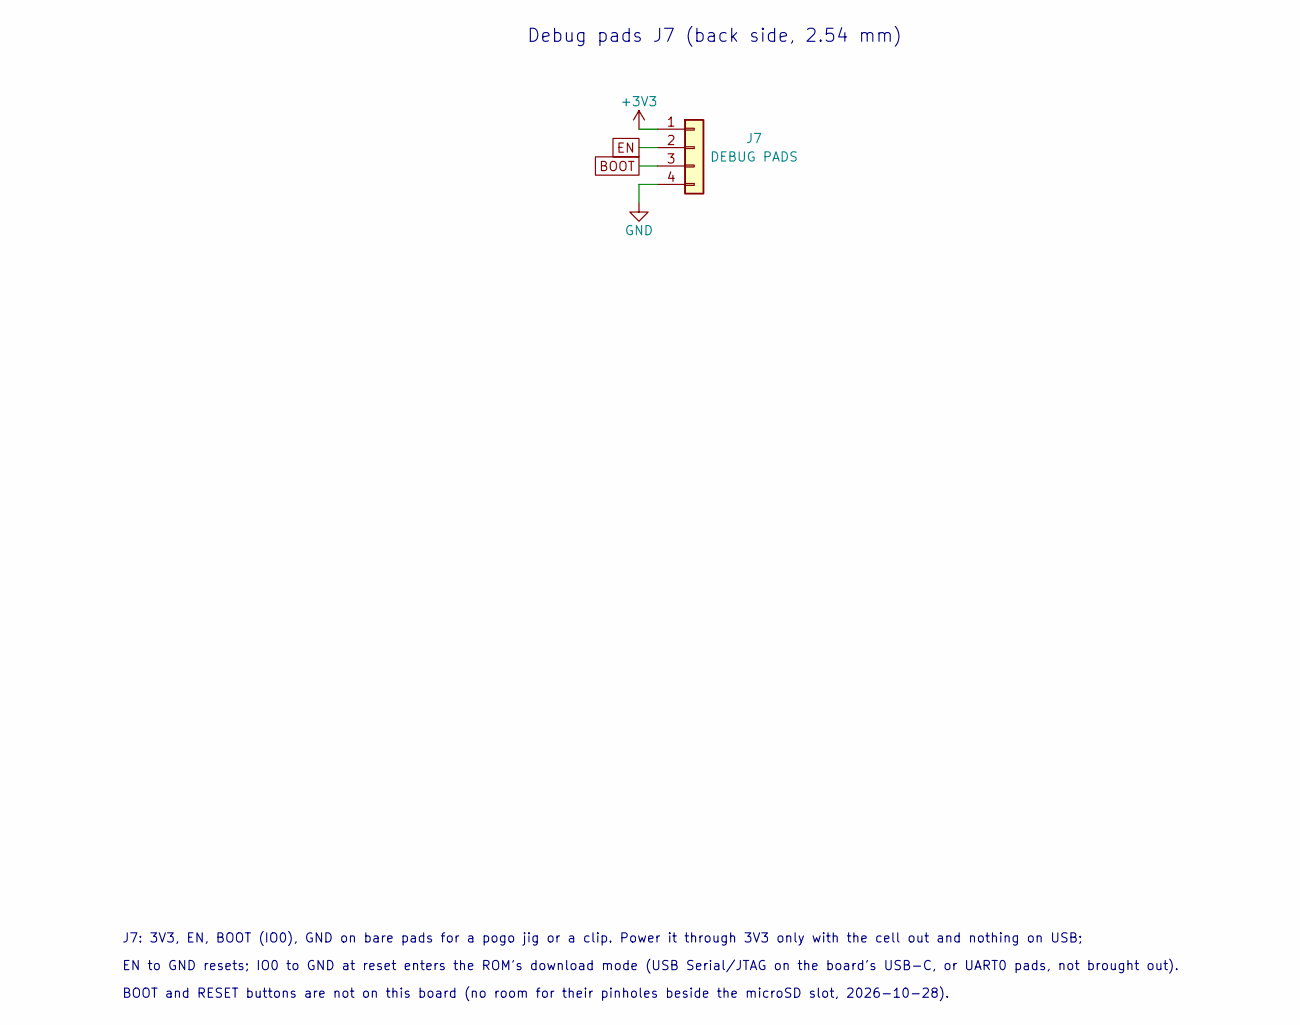
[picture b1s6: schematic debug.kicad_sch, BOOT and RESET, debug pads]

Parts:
J7: DEBUG PADS; Pogo_Pads_1x04_P2.54mm

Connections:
+3V3: J7.1; also elsewhere on the board
BOOT: J7.3; also elsewhere on the board
EN: J7.2; also elsewhere on the board
GND: J7.4; also elsewhere on the board

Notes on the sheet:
Debug pads J7 (back side, 2.54 mm)
J7: 3V3, EN, BOOT (IO0), GND on bare pads for a pogo jig or a clip. Power it through 3V3 only with the cell out and nothing on USB;
EN to GND resets; IO0 to GND at reset enters the ROM's download mode (USB Serial/JTAG on the board's USB-C, or UART0 pads, not brought out).
BOOT and RESET buttons are not on this board (no room for their pinholes beside the microSD slot, 2026-10-28).

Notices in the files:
hardware/ref_design/README.md:
`hardware/ref_design/datasheets/`). The vendored membrane footprints are public domain. DS Lite
